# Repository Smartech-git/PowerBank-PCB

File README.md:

# PowerBank-PCB-featuring-INJONIC-IP5328P
Design with KICad V6.0.6

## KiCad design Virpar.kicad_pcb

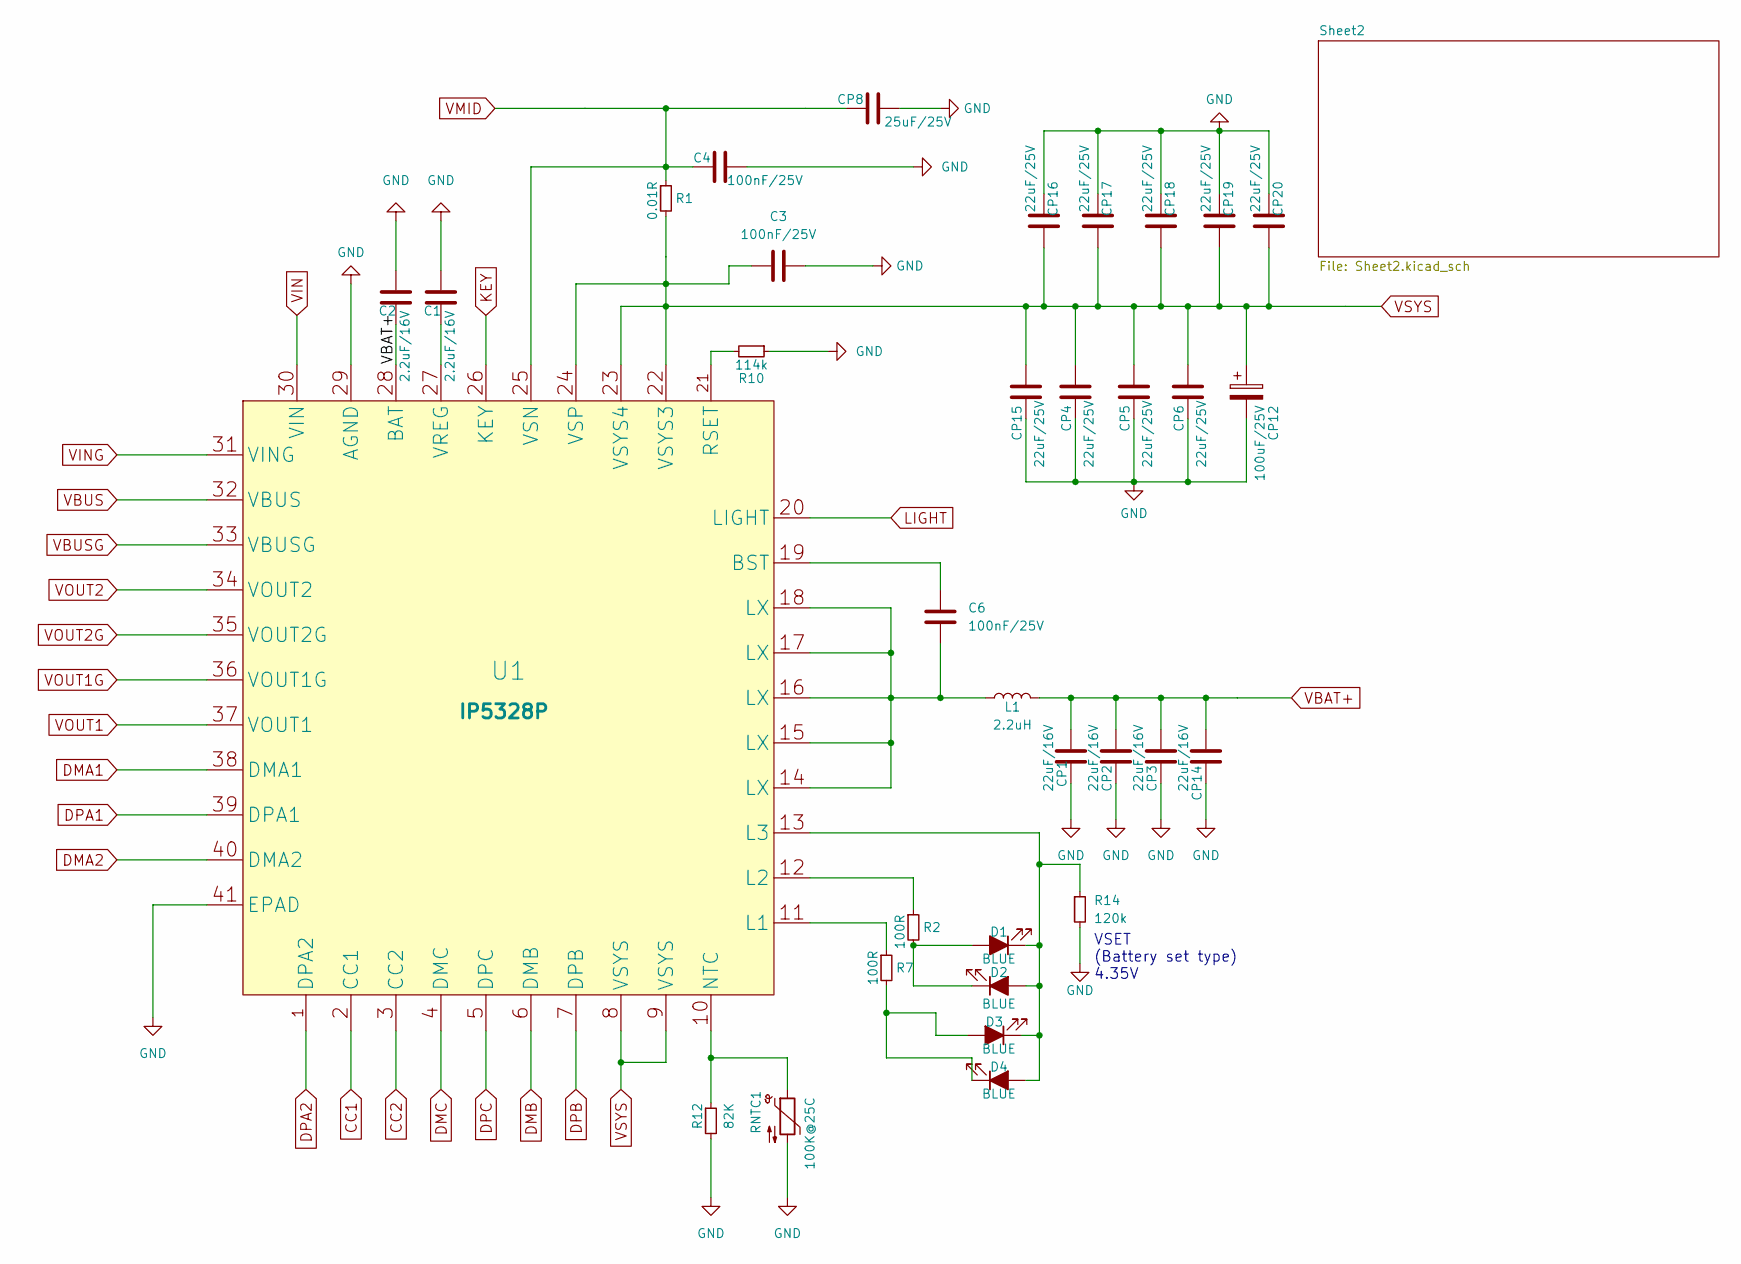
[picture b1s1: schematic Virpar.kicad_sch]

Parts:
C1, C2: 2.2uF/16V; C_0603_1608Metric_Pad1.08x0.95mm_HandSolder
C3, C4, C6: 100nF/25V; C_0603_1608Metric_Pad1.08x0.95mm_HandSolder
CP1, CP2, CP3, CP14: 22uF/16V; C_0805_2012Metric_Pad1.18x1.45mm_HandSolder
CP4, CP5, CP6, CP15, CP16, CP17, CP18, CP19, CP20: 22uF/25V; C_0805_2012Metric_Pad1.18x1.45mm_HandSolder
CP8: 25uF/25V; C_0805_2012Metric_Pad1.18x1.45mm_HandSolder
CP12: 100uF/25V; CP_Elec_8x6.9
D1, D2, D3, D4: BLUE; LED_0603_1608Metric_Pad1.05x0.95mm_HandSolder
L1: 2.2uH; L_10.4x10.4_H4.8
R1: 0.01R; R_1206_3216Metric_Pad1.30x1.75mm_HandSolder
R2, R7: 100R; R_0603_1608Metric_Pad0.98x0.95mm_HandSolder
R10: 114k; R_0603_1608Metric_Pad0.98x0.95mm_HandSolder
R12: 82K; R_0603_1608Metric_Pad0.98x0.95mm_HandSolder
R14: 120k; R_0603_1608Metric_Pad0.98x0.95mm_HandSolder
RNTC1: 100K@25C; R_0805_2012Metric_Pad1.20x1.40mm_HandSolder
U1: IP5328P; QFN-40-1EP_6x6mm_P0.5mm_EP4.6x4.6mm_ThermalVias

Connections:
CC1: U1.2 (CC1); also elsewhere on the board
CC2: U1.3 (CC2); also elsewhere on the board
DMA1: U1.38 (DMA1); also elsewhere on the board
DMA2: U1.40 (DMA2); also elsewhere on the board
DMB: U1.6 (DMB); also elsewhere on the board
DMC: U1.4 (DMC); also elsewhere on the board
DPA1: U1.39 (DPA1); also elsewhere on the board
DPA2: U1.1 (DPA2); also elsewhere on the board
DPB: U1.7 (DPB); also elsewhere on the board
DPC: U1.5 (DPC); also elsewhere on the board
GND: C1.1, C2.1, C3.2, C4.2, CP1.2, CP2.2, CP3.2, CP4.2, CP5.2, CP6.2, CP8.2, CP12.2, CP14.2, CP15.2, CP16.2, CP17.2, CP18.2, CP19.2, CP20.2, R10.1, R12.2, R14.2, RNTC1.2, U1.29 (AGND), U1.41 (EPAD); also elsewhere on the board
KEY: U1.26 (KEY); also elsewhere on the board
LIGHT: U1.20 (LIGHT); also elsewhere on the board
unnamed: C1.2, U1.27 (VREG)
unnamed: C6.1, U1.19 (BST)
unnamed: C6.2, L1.1, U1.14 (LX), U1.15 (LX), U1.16 (LX), U1.17 (LX), U1.18 (LX)
unnamed: D1.1 (K), D2.2 (A), D3.1 (K), D4.2 (A), R14.1, U1.13 (L3)
unnamed: D1.2 (A), D2.1 (K), R2.2
unnamed: D3.2 (A), D4.1 (K), R7.2
unnamed: R2.1, U1.12 (L2)
unnamed: R7.1, U1.11 (L1)
unnamed: R10.2, U1.21 (RSET)
unnamed: R12.1, RNTC1.1, U1.10 (NTC)
VBAT+: C2.2, CP1.1, CP2.1, CP3.1, CP14.1, L1.2, U1.28 (BAT); also elsewhere on the board
VBUS: U1.32 (VBUS); also elsewhere on the board
VBUSG: U1.33 (VBUSG); also elsewhere on the board
VIN: U1.30 (VIN); also elsewhere on the board
VING: U1.31 (VING); also elsewhere on the board
VMID: C4.1, CP8.1, R1.1, U1.25 (VSN); also elsewhere on the board
VOUT1: U1.37 (VOUT1); also elsewhere on the board
VOUT1G: U1.36 (VOUT1G); also elsewhere on the board
VOUT2: U1.34 (VOUT2); also elsewhere on the board
VOUT2G: U1.35 (VOUT2G); also elsewhere on the board
VSYS: C3.1, CP4.1, CP5.1, CP6.1, CP12.1, CP15.1, CP16.1, CP17.1, CP18.1, CP19.1, CP20.1, R1.2, U1.8 (VSYS), U1.9 (VSYS), U1.22 (VSYS3), U1.23 (VSYS4), U1.24 (VSP); also elsewhere on the board

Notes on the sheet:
VSET (Battery set type) 4.35V

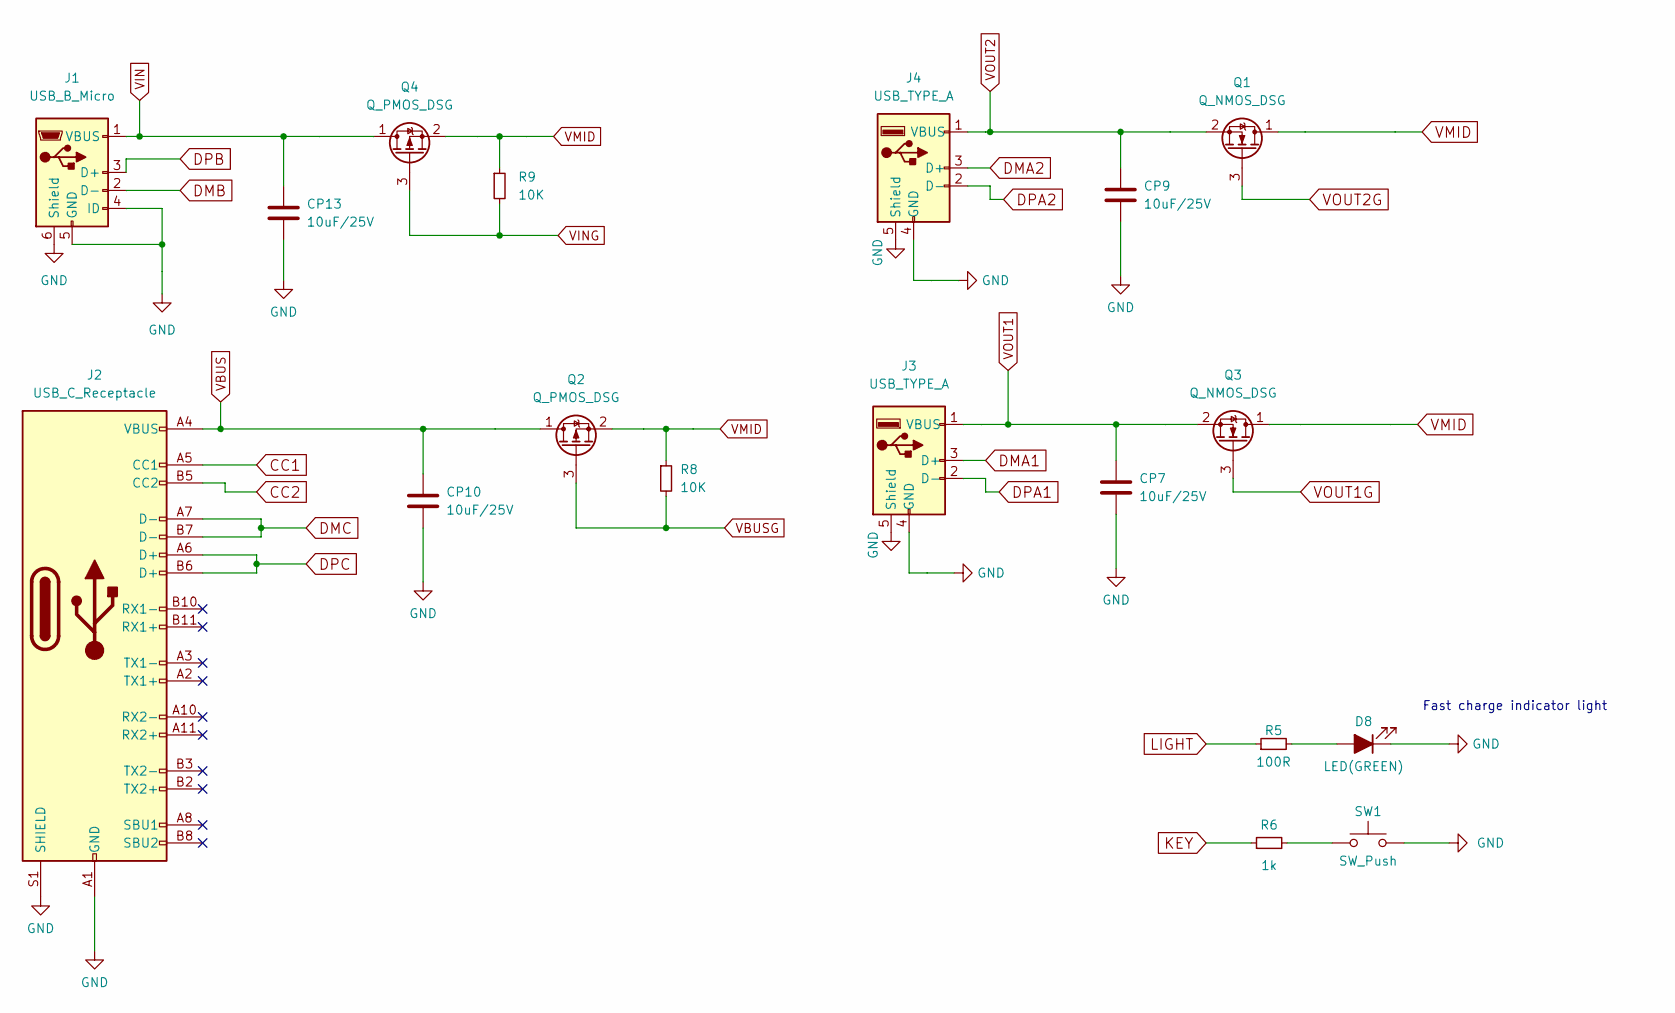
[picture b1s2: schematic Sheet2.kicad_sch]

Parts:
CP7, CP9, CP10, CP13: 10uF/25V; C_0805_2012Metric_Pad1.18x1.45mm_HandSolder
D8: LED(GREEN); LED_0805_2012Metric_Pad1.15x1.40mm_HandSolder
J1: USB_B_Micro; USB_Micro-AB_Molex_47590-0001
J2: USB_C_Receptacle; 632723100011 USB C Receptacle Wurth
J3, J4: USB_TYPE_A; GCT_USB1020-XX-X-X_REVA3
Q1, Q3: Q_NMOS_DSG; TSOT-23
Q2, Q4: Q_PMOS_DSG; TSOT-23
R5: 100R; R_0603_1608Metric_Pad0.98x0.95mm_HandSolder
R6: 1k; R_0603_1608Metric_Pad0.98x0.95mm_HandSolder
R8, R9: 10K; R_0603_1608Metric_Pad0.98x0.95mm_HandSolder
SW1: SW_Push; tactile micro switch

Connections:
CC1: J2.A5 (CC1); also elsewhere on the board
CC2: J2.B5 (CC2); also elsewhere on the board
DMA1: J3.3 (D+); also elsewhere on the board
DMA2: J4.3 (D+); also elsewhere on the board
DMB: J1.2 (D-); also elsewhere on the board
DMC: J2.A7 (D-), J2.B7 (D-); also elsewhere on the board
DPA1: J3.2 (D-); also elsewhere on the board
DPA2: J4.2 (D-); also elsewhere on the board
DPB: J1.3 (D+); also elsewhere on the board
DPC: J2.A6 (D+), J2.B6 (D+); also elsewhere on the board
GND: CP7.2, CP9.2, CP10.2, CP13.2, D8.1 (K), J1.4 (ID), J1.5 (GND), J1.6 (Shield), J2.A1 (GND), J2.A12 (GND), J2.B1 (GND), J2.B12 (GND), J2.S1 (SHIELD), J3.4 (GND), J3.5 (Shield), J4.4 (GND), J4.5 (Shield), SW1.2; also elsewhere on the board
KEY: R6.1; also elsewhere on the board
LIGHT: R5.1; also elsewhere on the board
unnamed: D8.2 (A), R5.2
unnamed: R6.2, SW1.1
VBUS: CP10.1, J2.A4 (VBUS), J2.A9 (VBUS), J2.B4 (VBUS), J2.B9 (VBUS), Q2.1 (D); also elsewhere on the board
VBUSG: Q2.3 (G), R8.2; also elsewhere on the board
VIN: CP13.1, J1.1 (VBUS), Q4.1 (D); also elsewhere on the board
VING: Q4.3 (G), R9.2; also elsewhere on the board
VMID: Q1.1 (D), Q2.2 (S), Q3.1 (D), Q4.2 (S), R8.1, R9.1; also elsewhere on the board
VOUT1: CP7.1, J3.1 (VBUS), Q3.2 (S); also elsewhere on the board
VOUT1G: Q3.3 (G); also elsewhere on the board
VOUT2: CP9.1, J4.1 (VBUS), Q1.2 (S); also elsewhere on the board
VOUT2G: Q1.3 (G); also elsewhere on the board

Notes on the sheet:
Fast charge indicator light

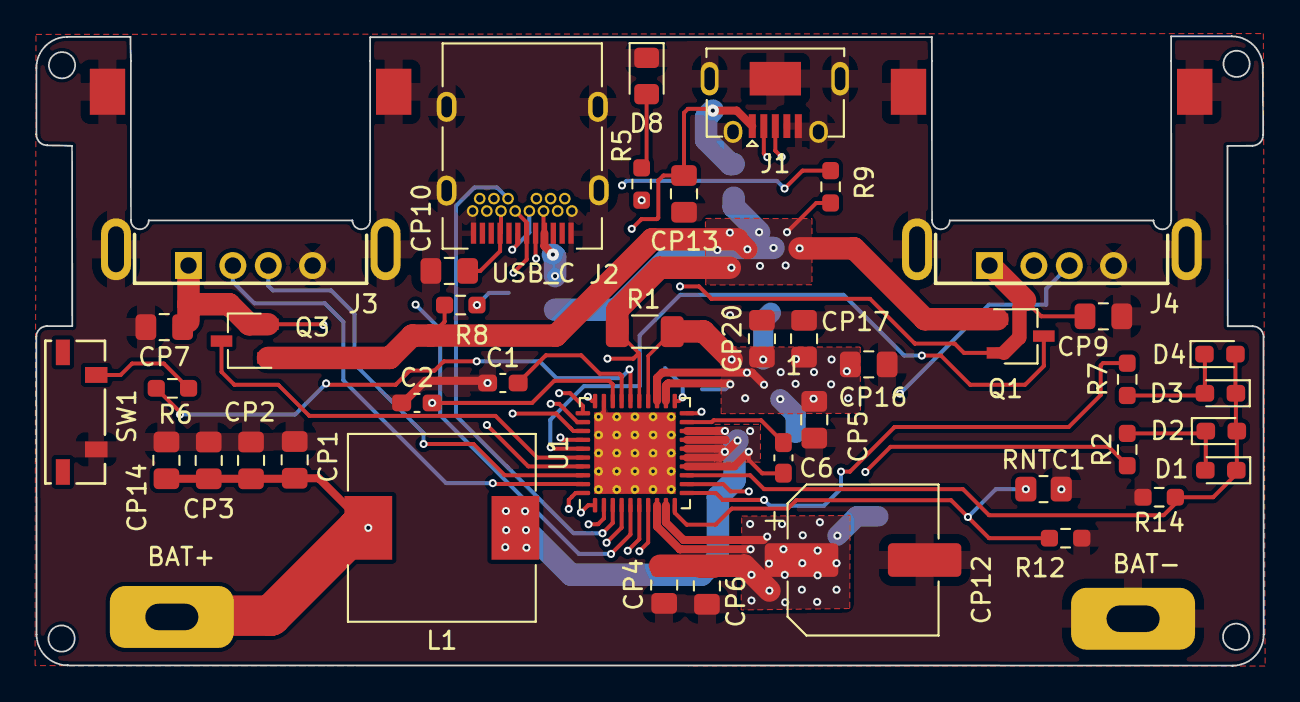
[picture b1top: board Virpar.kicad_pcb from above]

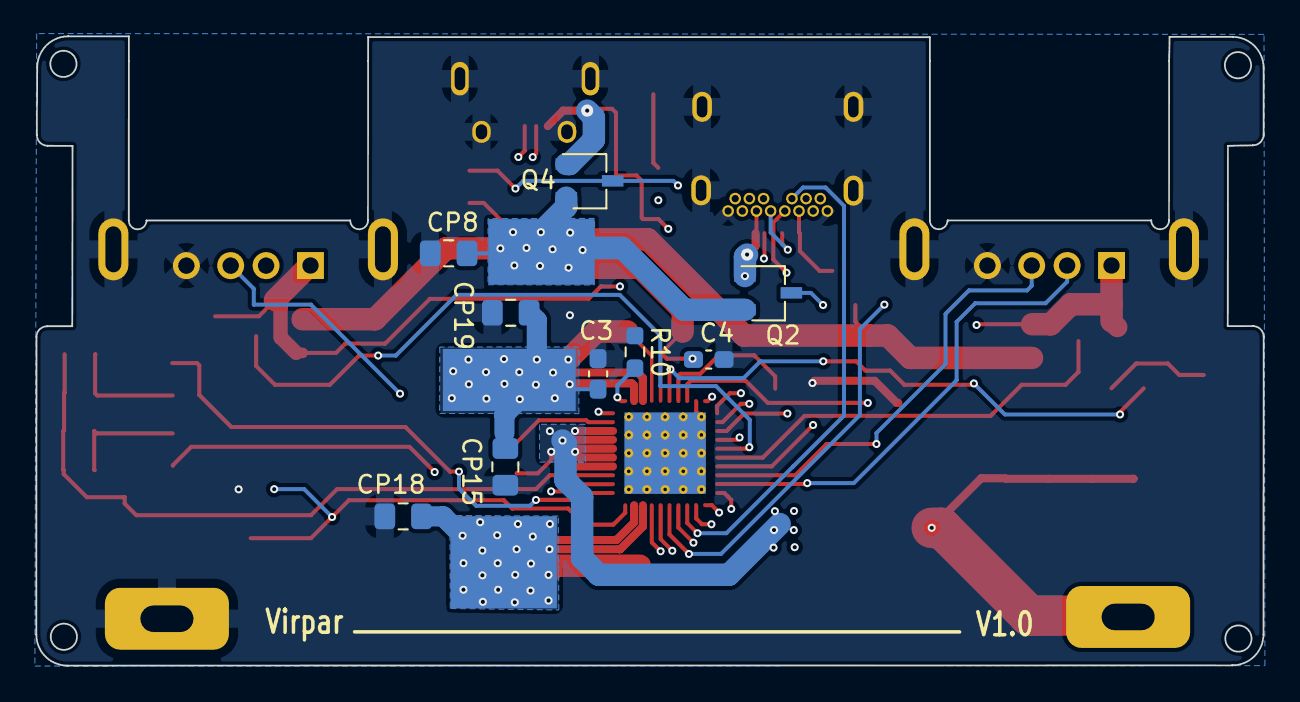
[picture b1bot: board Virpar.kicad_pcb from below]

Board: 4 copper layers, 69.3 x 35.5 mm, 56 parts (9 on the bottom side), 36 nets.

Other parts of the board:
1, 2, 3: Heat pads
BAT+: BAT Pads
BAT-: BAT Pads

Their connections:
GND: BAT-.1; also elsewhere on the board
VBAT+: BAT+.1; also elsewhere on the board
VMID: 2.1; also elsewhere on the board
VSYS: 1.1, 3.1; also elsewhere on the board
